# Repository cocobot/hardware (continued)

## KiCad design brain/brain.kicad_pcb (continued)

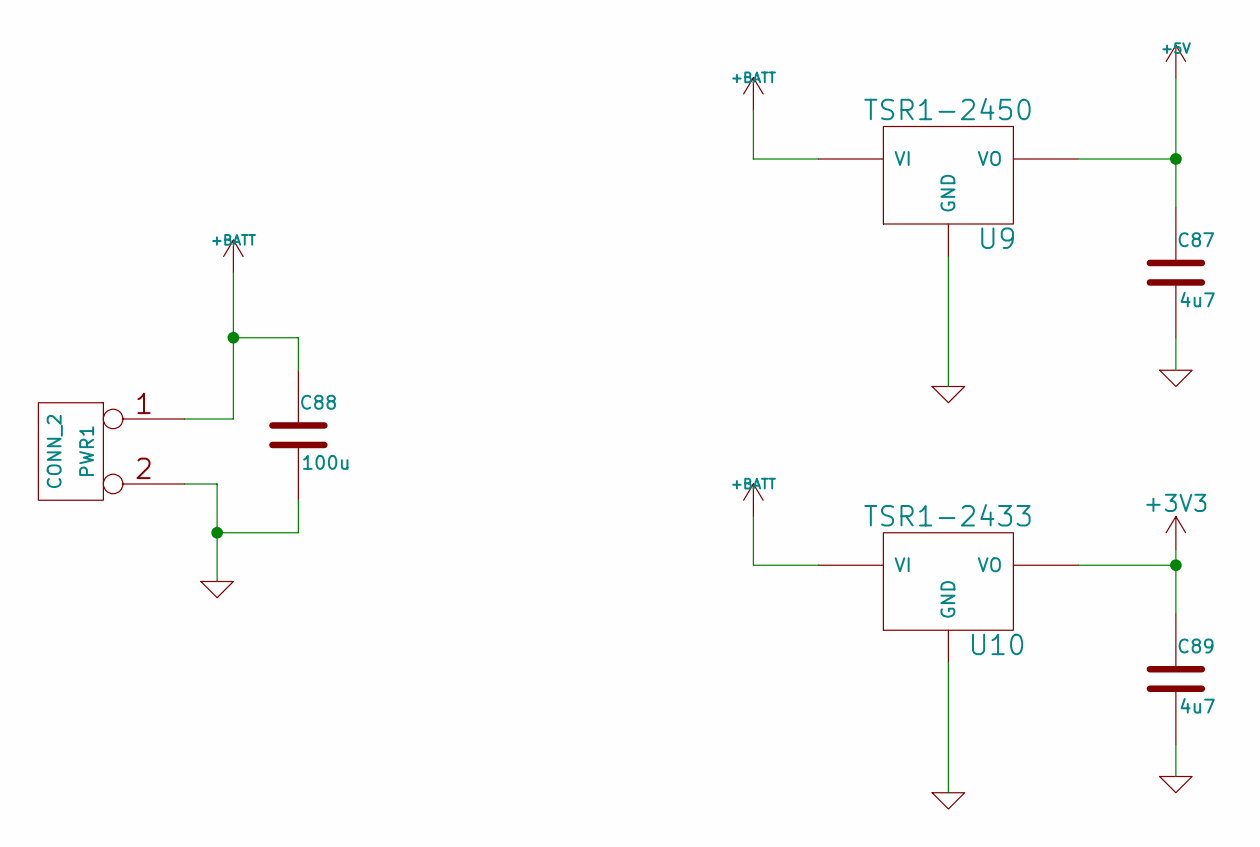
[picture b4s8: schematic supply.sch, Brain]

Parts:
C87, C89: 4u7; C_0603
C88: 100u; c_elec_6.3x7.7
PWR1: CONN_2; Socket_MOLEX-KK-RM2-54mm_Lock_2pin_straight
U9: TSR1-2450; TSR-1
U10: TSR1-2433; TSR-1

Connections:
+3V3: C89.1, U10.3 (VO); also elsewhere on the board
+5V: C87.1, U9.3 (VO); also elsewhere on the board
+BATT: C88.1, PWR1.1, U9.1 (VI), U10.1 (VI); also elsewhere on the board
GND: C87.2, C88.2, C89.2, PWR1.2 (PM), U9.2 (GND), U10.2 (GND); also elsewhere on the board

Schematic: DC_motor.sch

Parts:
C30: 4u7; C_0603
DCM0: CONN_5; Socket_MOLEX-KK-RM2-54mm_Lock_5pin_straight

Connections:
+5V: C30.1, DCM0.1; also elsewhere on the board
/DC motor/DCM0_DIR_3v3: DCM0.3; also elsewhere on the board
/DC motor/DCM0_PWM_3v3: DCM0.4; also elsewhere on the board
/DC motor/MOT_ENA_3v3: DCM0.2; also elsewhere on the board
GND: C30.2, DCM0.5; also elsewhere on the board

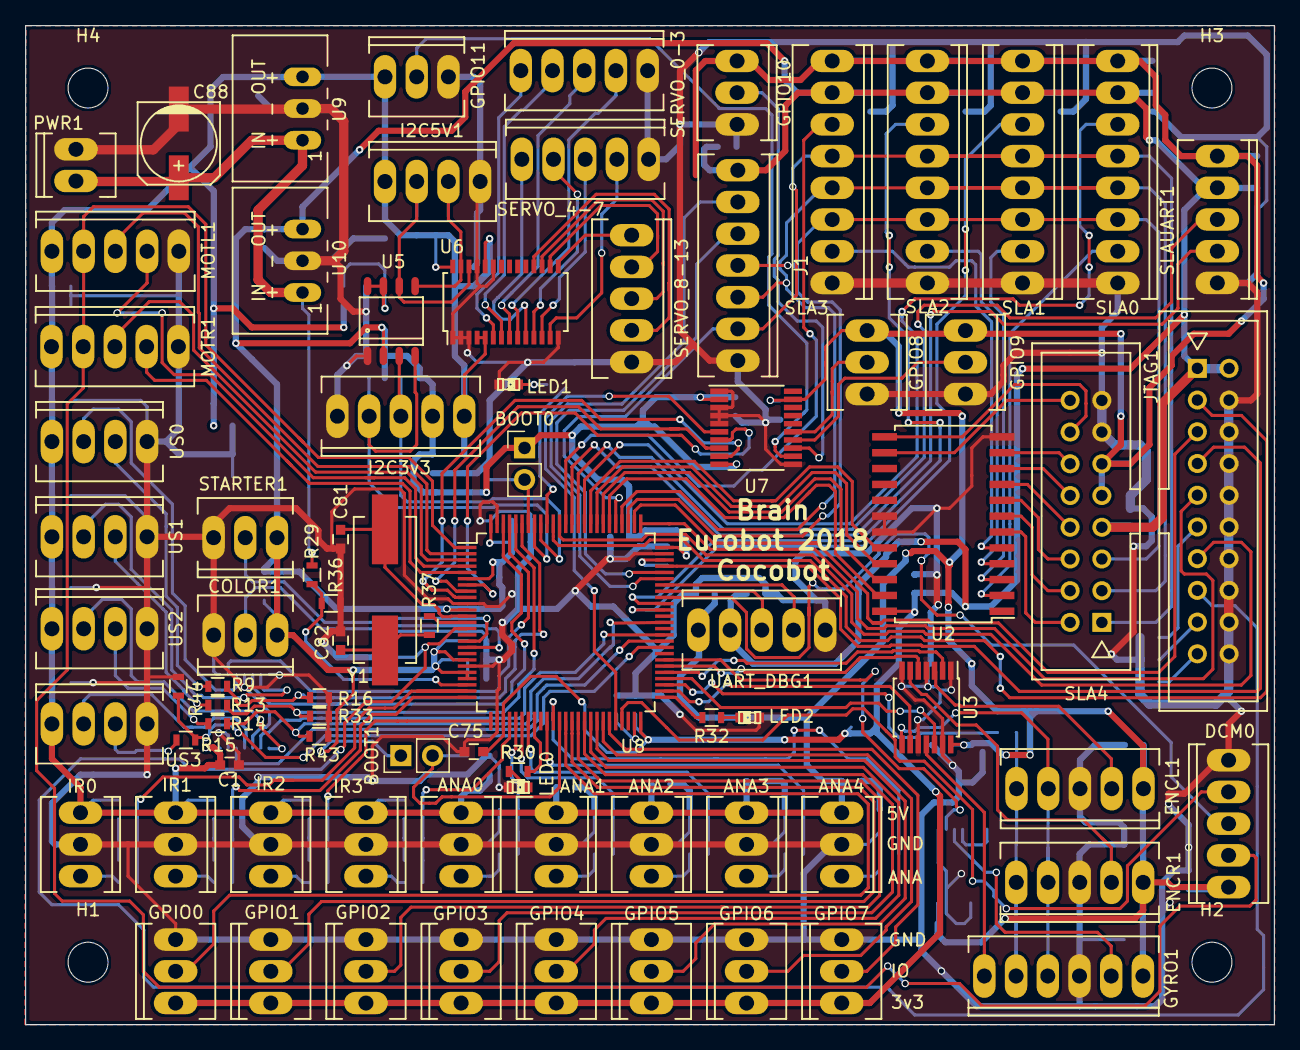
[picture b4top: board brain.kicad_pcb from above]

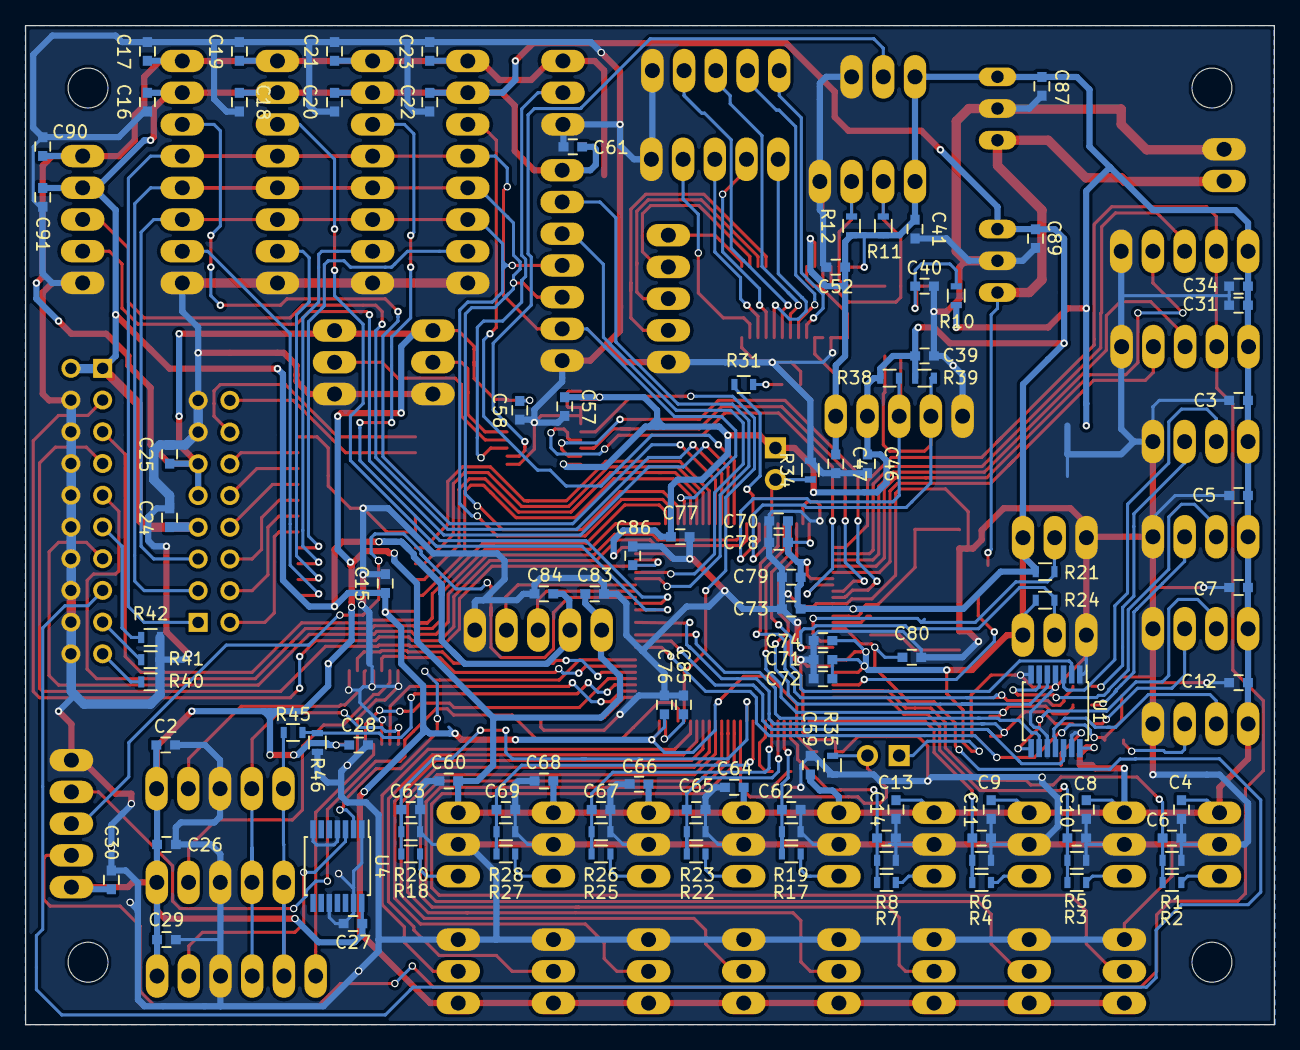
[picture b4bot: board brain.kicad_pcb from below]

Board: 2 copper layers, 100.0 x 80.0 mm, 187 parts (103 on the bottom side), 144 nets.

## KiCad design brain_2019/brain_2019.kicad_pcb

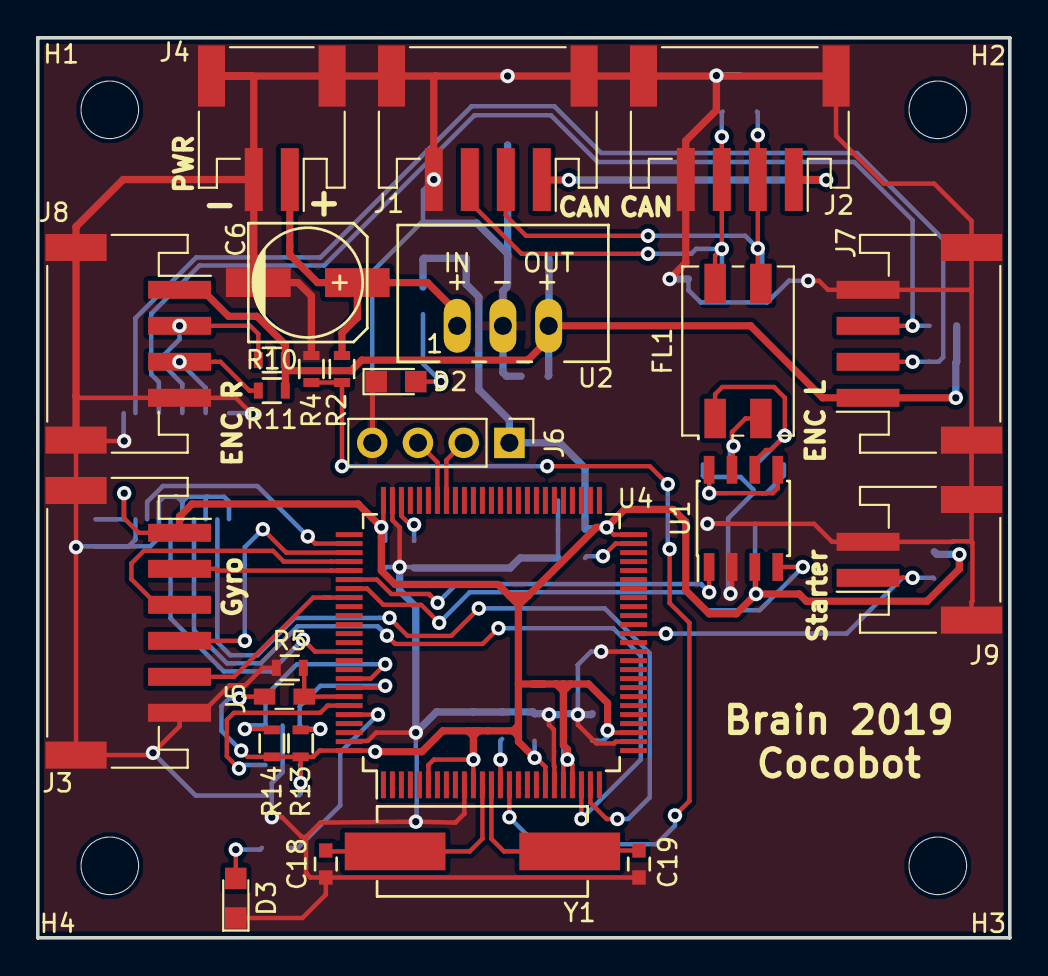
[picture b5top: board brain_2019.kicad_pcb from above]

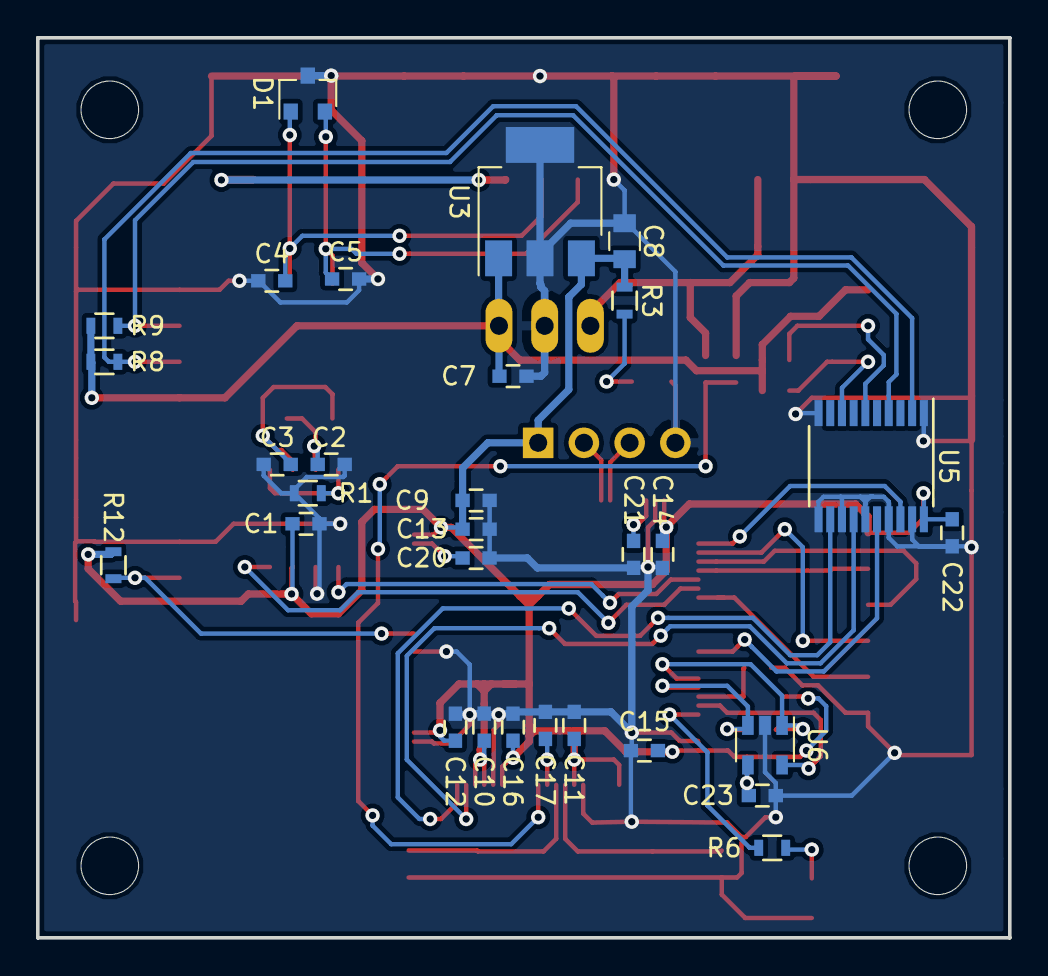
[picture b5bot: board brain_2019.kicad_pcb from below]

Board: 2 copper layers, 54.0 x 50.0 mm, 60 parts (30 on the bottom side), 40 nets.

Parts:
C1, C10, C11, C12, C13, C14, C15, C16, C17, C22, C23: 100n; C_0603
C2, C3, C4, C5: C; C_0603
C6: CP; c_elec_6.3x7.7
C7, C20, C21: 2u2; C_0603
C8: 47u; C_0805
C9: 10u; C_0603
C18, C19: 20p; C_0603
D1: NUP2105LT1G; SOT-23
D2, D3: LED; LED_0805
FL1: DR331-113BE; DR331
H1, H2, H3, H4: Conn_01x01; MountingHole_3.2mm_M3
J1, J2: CocobotCAN; JST_PH_S4B-PH-SM4-TB_04x2.00mm_Angled
J3: JST_PH_S6B-PH-SM4-TB_06x2.00mm_Angled
J4, J9: JST_PH_S2B-PH-SM4-TB_02x2.00mm_Angled
J5: Conn_01x02; R_0603_HandSoldering
J6: Conn_01x04; Socket_Strip_Straight_1x04_Pitch2.54mm
J7, J8: JST_PH_S4B-PH-SM4-TB_04x2.00mm_Angled
R1: 0; R_0603
R2, R5, R12: 10k; R_0603
R3, R6: 220; R_0603
R4: 1k; R_0603
R8, R9, R10, R11: R; R_0603
R13, R14: 2k2; R_0603
U1: MAX3051ESA; SOIC-8_3.9x4.9mm_Pitch1.27mm
U2: TSR1-2450; TSR-1
U3: LM3940IMP-3.3; SOT-223-3_TabPin2
U4: STM32F407VG; LQFP-100_14x14mm_Pitch0.5mm
U5: MC74VHC244DTG; TSSOP-20_4.4x6.5mm_Pitch0.65mm
U6: 24LC64T-I; SOT-23-5
Y1: 8M; Crystal_HC49-SD_SMD

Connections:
+3V3: C1.1, C8.1, C9.1, C10.1, C11.1, C12.1, C13.1, C14.1, C15.1, C16.1, C22.2, C23.1, J3.1, J5.1, J6.1, R3.1, R12.1, R13.1, R14.1, U1.3, U3.3, U4.6, U4.11, U4.19, U4.21, U4.22, U4.28, U4.50, U4.75, U4.100, U5.20, U6.4
+5V: C7.1, J7.1, J8.1, R8.1, R9.1, R10.1, R11.1, U2.3, U3.1
+BATT: C6.1, J4.1, R2.1, U2.1
/CAN/can_rx_3v3: U1.4, U4.82
/CAN/can_tx_3v3: U1.1, U4.81
/Encoders/enc_l_A_3v3: U4.77, U5.18
/Encoders/enc_l_A_5v: J7.2, R8.2, U5.2
/Encoders/enc_l_B_3v3: U4.89, U5.16
/Encoders/enc_l_B_5v: J7.3, R9.2, U5.4
/Encoders/enc_r_A_3v3: U4.23, U5.14
/Encoders/enc_r_A_5v: J8.2, R10.2, U5.6
/Encoders/enc_r_B_3v3: U4.24, U5.12
/Encoders/enc_r_B_5v: J8.3, R11.2, U5.8
/Gyro/miso_3v3: J3.3, U4.79
/Gyro/mosi_3v3: J3.2, U4.80
/Gyro/sck_3v3: J3.4, U4.78
/IO/starter_3v3: J9.1, R12.2, U4.39
/Supply/vbatmon_0-3v3: R2.2, R4.1, U4.15
/uc/BOOT0_3v3: J5.2, R5.1, U4.94
/uc/nSRST_3v3: C17.1, U4.14
/uc/spi_gyro_~cs~_3v3: J3.5, U4.83
GND: C1.2, C2.2, C3.2, C4.2, C5.2, C6.2, C7.2, C8.2, C9.2, C10.2, C11.2, C12.2, C13.2, C14.2, C15.2, C16.2, C17.2, C18.2, C19.2, C20.2, C21.2, C22.1, C23.2, D1.3, D2.1, D3.1, J1.4, J1.case, J2.4, J2.case, J3.6, J3.case, J4.2, J4.case, J6.4, J7.4, J7.case, J8.4, J8.case, J9.2, J9.case, R1.2, R4.2, R5.2, U1.2, U2.2, U3.2, U4.10, U4.20, U4.27, U4.37, U4.74, U4.99, U5.1, U5.10, U5.11, U5.13, U5.15, U5.17, U5.19, U6.2
unnamed: C2.1, FL1.2, U1.7
unnamed: C3.1, FL1.1, U1.6
unnamed: C4.1, D1.1, FL1.3, J1.2, J2.2
unnamed: C5.1, D1.2, FL1.4, J1.3, J2.3
unnamed: C18.1, U4.12, Y1.1
unnamed: C19.1, U4.13, Y1.2
unnamed: C20.1, U4.49
unnamed: C21.1, U4.73
unnamed: D2.2, R3.2
unnamed: D3.2, R6.2
unnamed: J1.1, J2.1
unnamed: J6.2, U4.68
unnamed: J6.3, U4.69
unnamed: R1.1, U1.5, U1.8
unnamed: R6.1, U4.96
unnamed: R13.2, U4.93, U6.3
unnamed: R14.2, U4.92, U6.1
unnamed: U4.95, U6.5

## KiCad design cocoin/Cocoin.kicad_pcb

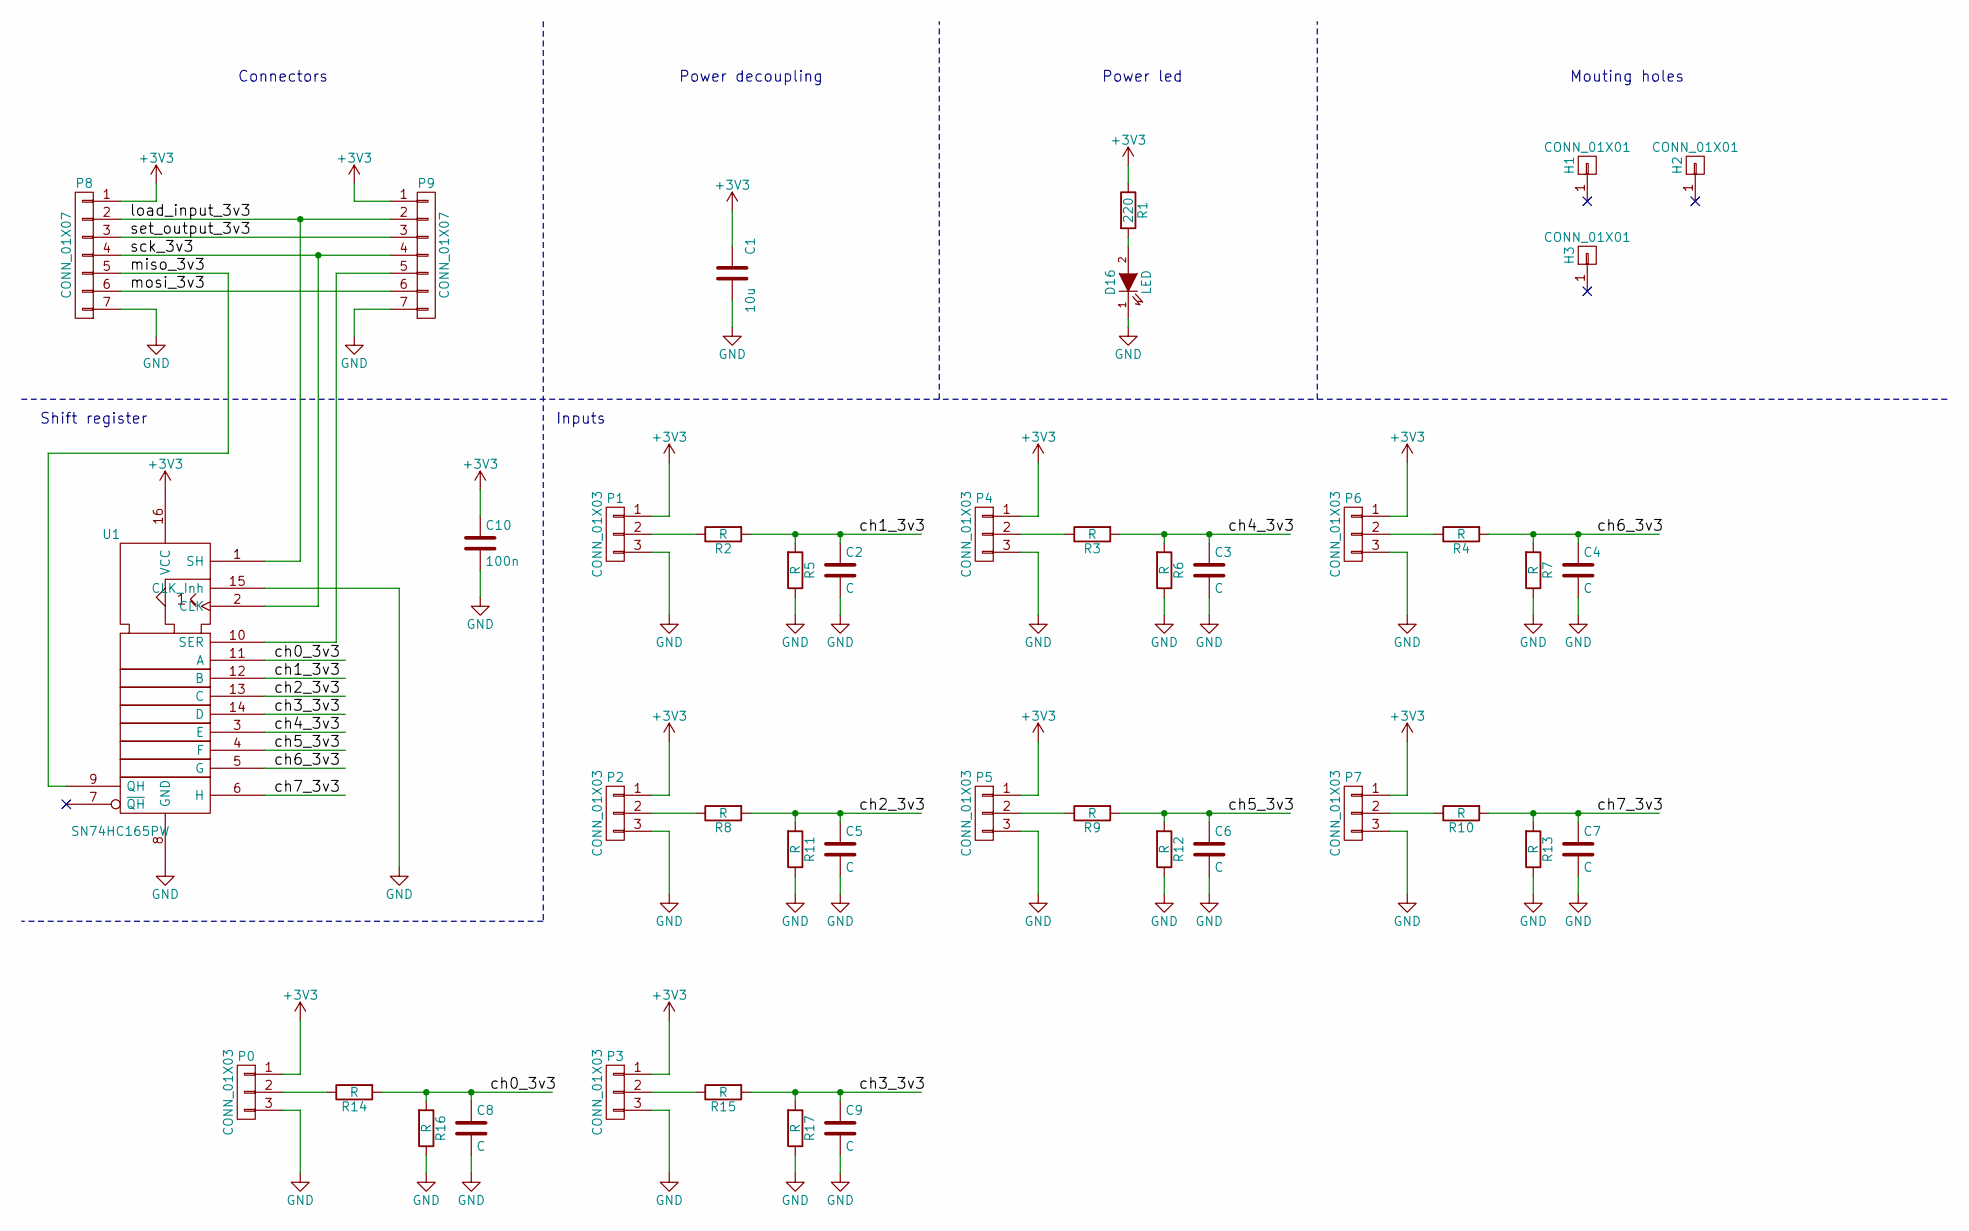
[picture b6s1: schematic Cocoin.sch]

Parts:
C1: 10u; C_0805_HandSoldering
C2, C3, C4, C5, C6, C7, C8, C9: C; C_0603_HandSoldering
C10: 100n; C_0603_HandSoldering
D16: LED; LED_0805
H1, H2, H3: CONN_01X01; MountingHole_3.2mm_M3
P0, P1, P2, P3, P4, P5, P6, P7: CONN_01X03; Socket_MOLEX-KK-RM2-54mm_Lock_3pin_straight
P8, P9: CONN_01X07; Socket_MOLEX-KK-RM2-54mm_Lock_7pin_straight
R1: 220; R_0603_HandSoldering
R2, R3, R4, R5, R6, R7, R8, R9, R10, R11, R12, R13, R14, R15, R16, R17: R; R_0603_HandSoldering
U1: SN74HC165PW; TSSOP-16_4.4x5mm_Pitch0.65mm

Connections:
+3V3: C1.1, C10.1, P0.1, P1.1, P2.1, P3.1, P4.1, P5.1, P6.1, P7.1, P8.1, P9.1, R1.1, U1.16 (VCC)
/ch0_3v3: C8.1, R14.2, R16.2, U1.11 (A)
/ch1_3v3: C2.1, R2.2, R5.2, U1.12 (B)
/ch2_3v3: C5.1, R8.2, R11.2, U1.13 (C)
/ch3_3v3: C9.1, R15.2, R17.2, U1.14 (D)
/ch4_3v3: C3.1, R3.2, R6.2, U1.3 (E)
/ch5_3v3: C6.1, R9.2, R12.2, U1.4 (F)
/ch6_3v3: C4.1, R4.2, R7.2, U1.5 (G)
/ch7_3v3: C7.1, R10.2, R13.2, U1.6 (H)
/load_input_3v3: P8.2, P9.2, U1.1 (SH)
/miso_3v3: P8.5, U1.9 (QH)
/mosi_3v3: P8.6, P9.6
/sck_3v3: P8.4, P9.4, U1.2 (CLK)
/set_output_3v3: P8.3, P9.3
GND: C1.2, C2.2, C3.2, C4.2, C5.2, C6.2, C7.2, C8.2, C9.2, C10.2, D16.1 (K), P0.3, P1.3, P2.3, P3.3, P4.3, P5.3, P6.3, P7.3, P8.7, P9.7, R5.1, R6.1, R7.1, R11.1, R12.1, R13.1, R16.1, R17.1, U1.8 (GND), U1.15 (CLK_Inh)
unnamed: D16.2 (A), R1.2
unnamed: P0.2, R14.1
unnamed: P1.2, R2.1
unnamed: P2.2, R8.1
unnamed: P3.2, R15.1
unnamed: P4.2, R3.1
unnamed: P5.2, R9.1
unnamed: P6.2, R4.1
unnamed: P7.2, R10.1
unnamed: P9.5, U1.10 (SER)

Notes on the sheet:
Connectors
Power decoupling
Mouting holes
Power led
Inputs
Shift register

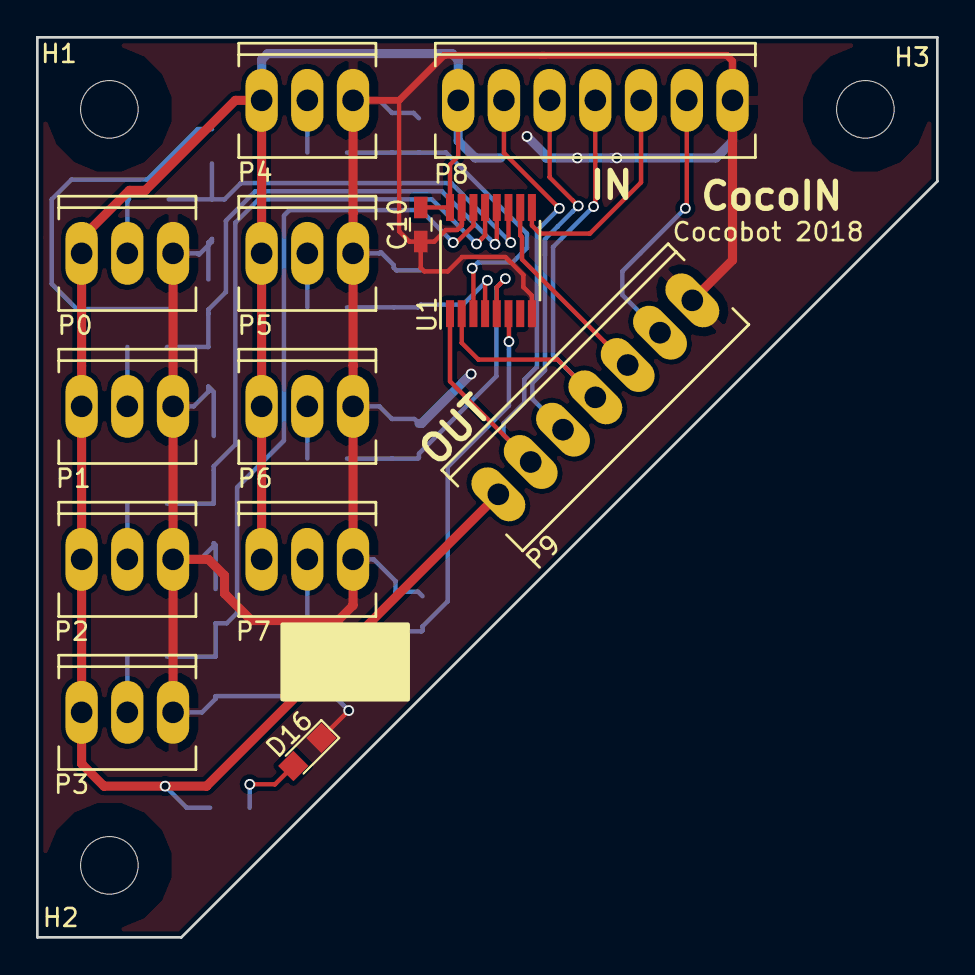
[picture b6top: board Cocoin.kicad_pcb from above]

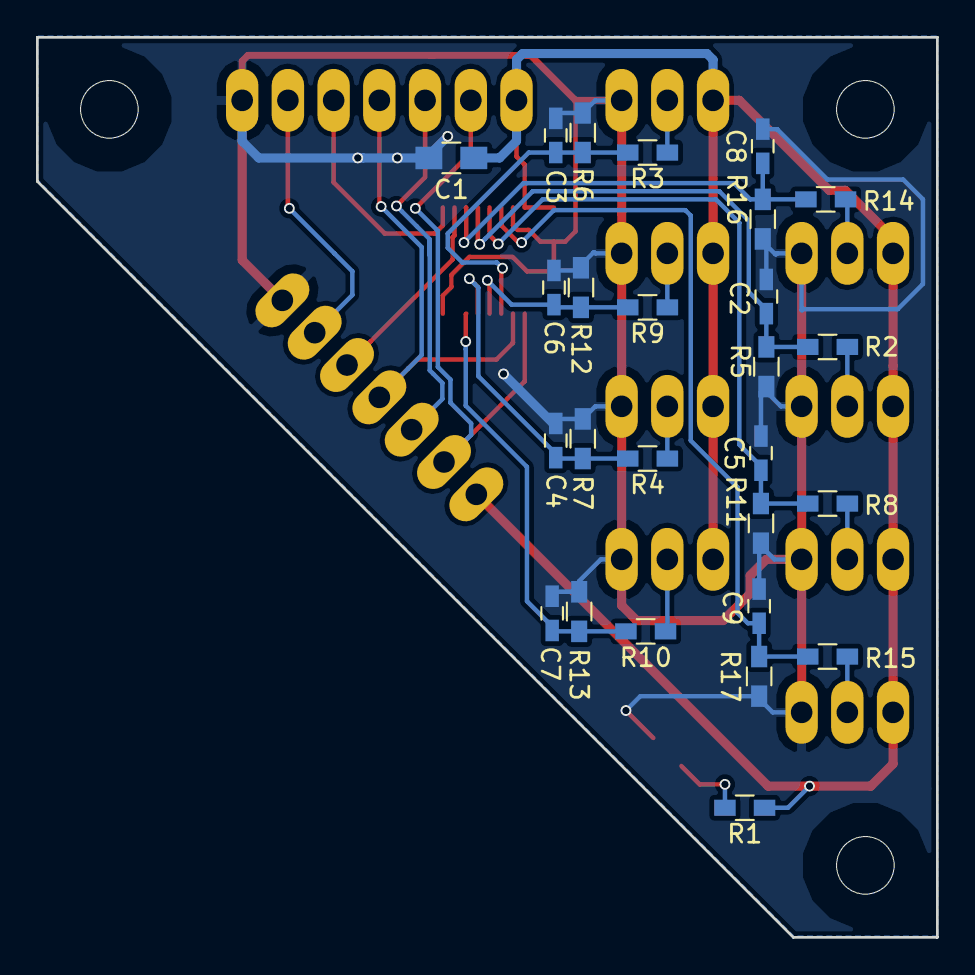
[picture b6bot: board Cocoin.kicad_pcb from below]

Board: 2 copper layers, 50.0 x 50.0 mm, 42 parts (26 on the bottom side), 25 nets.

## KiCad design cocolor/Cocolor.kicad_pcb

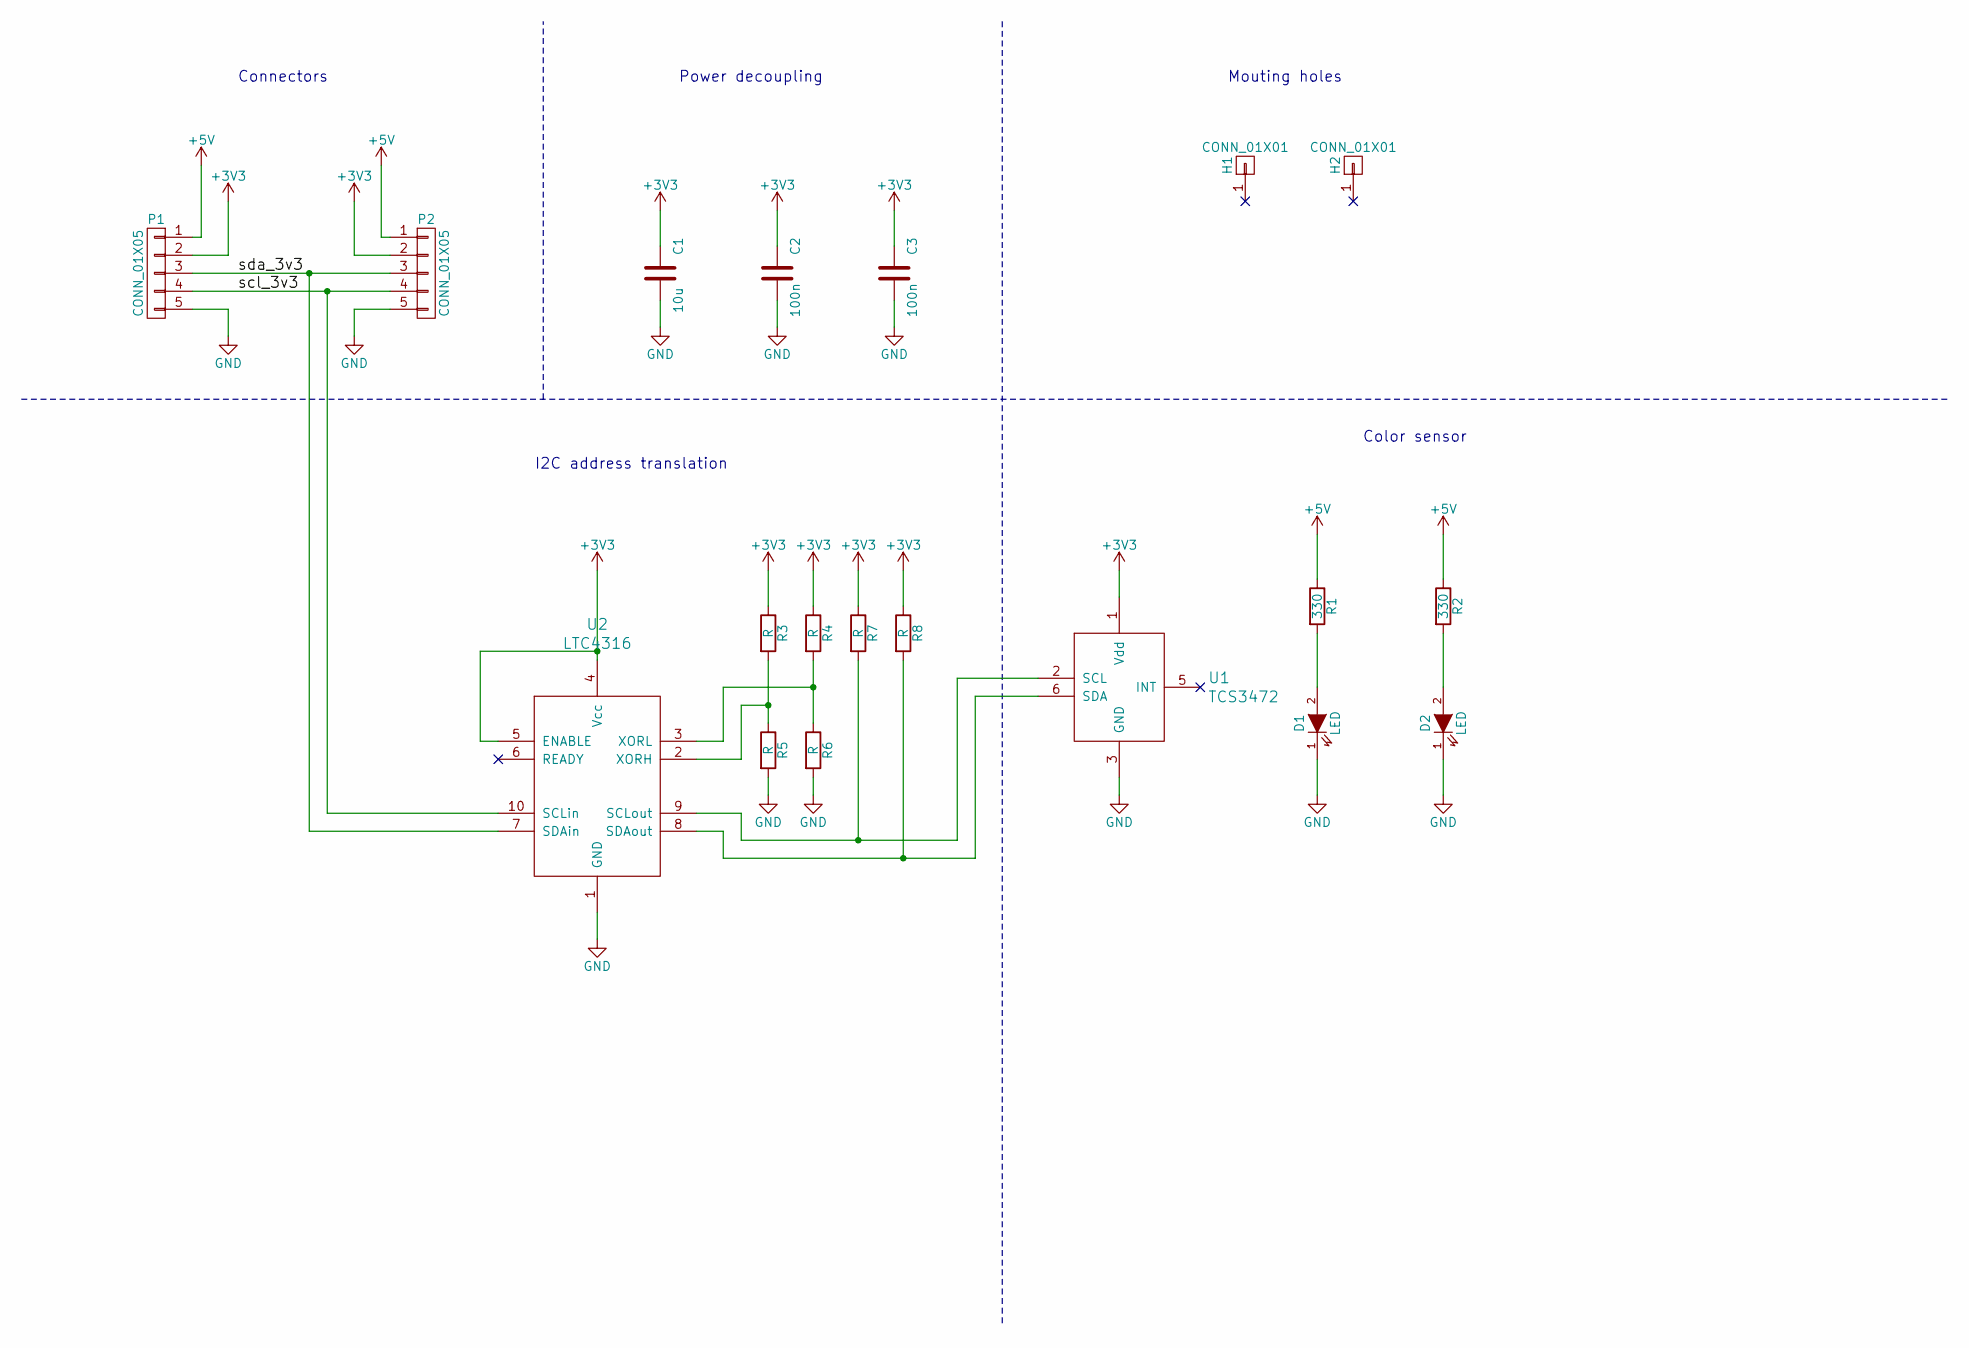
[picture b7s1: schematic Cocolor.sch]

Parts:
C1: 10u; C_0805_HandSoldering
C2, C3: 100n; C_0603_HandSoldering
D1, D2: LED; LED_1206
H1, H2: CONN_01X01; MountingHole_3.2mm_M3
P1, P2: CONN_01X05; Socket_MOLEX-KK-RM2-54mm_Lock_5pin_straight
R1, R2: 330; R_0603_HandSoldering
R3, R4, R5, R6, R7, R8: R; R_0603_HandSoldering
U1: TCS3472; DFN-6
U2: LTC4316; MSOP-10

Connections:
+3V3: C1.1, C2.1, C3.1, P1.2, P2.2, R3.1, R4.1, R7.1, R8.1, U1.1 (Vdd), U2.4 (Vcc), U2.5 (ENABLE)
+5V: P1.1, P2.1, R1.1, R2.1
/scl_3v3: P1.4, P2.4, U2.10 (SCLin)
/sda_3v3: P1.3, P2.3, U2.7 (SDAin)
GND: C1.2, C2.2, C3.2, D1.1 (K), D2.1 (K), P1.5, P2.5, R5.2, R6.2, U1.3 (GND), U2.1 (GND)
unnamed: D1.2 (A), R1.2
unnamed: D2.2 (A), R2.2
unnamed: R3.2, R5.1, U2.2 (XORH)
unnamed: R4.2, R6.1, U2.3 (XORL)
unnamed: R7.2, U1.2 (SCL), U2.9 (SCLout)
unnamed: R8.2, U1.6 (SDA), U2.8 (SDAout)

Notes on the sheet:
Connectors
Power decoupling
I2C address translation
Color sensor
Mouting holes

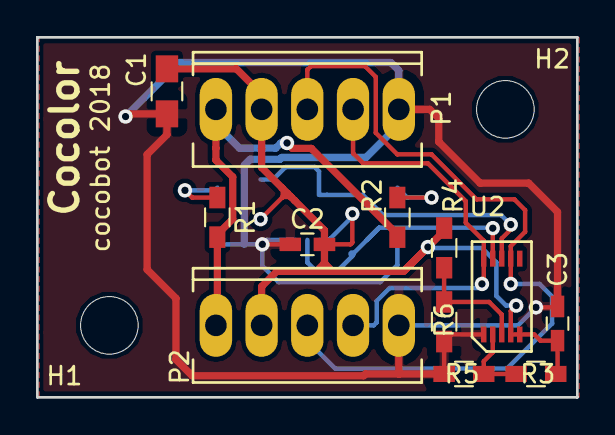
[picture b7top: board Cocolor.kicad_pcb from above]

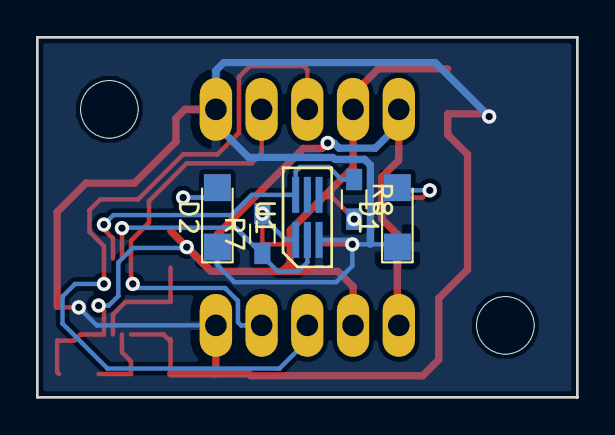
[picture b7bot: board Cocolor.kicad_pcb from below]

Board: 2 copper layers, 30.0 x 20.0 mm, 19 parts (5 on the bottom side), 11 nets.
